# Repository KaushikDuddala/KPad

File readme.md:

# KPad v1!

The KPad is a simple macropad made by me just to learn the process and hopefully make revisions or a full keyboard in the future!! This was made using KMK, KiCad, Fusion 360, and more. 

## Features:

 - 128x32 OLED with volume display
 - EC11 Encoder for Volume
 - 16 SK6812 LEDs for underglow!!
 - 8 keys + physical key in the ec11
 - KMK firmware

 ## Future Features:
 - Swappable Modes (Single key swaps a mode that chaanges all key functions)
 - VIA support
 - Better software LED control
 - Better case design
 - Acrylic rather than hole in case

## Final Design

## PCB Design:

## Case:

## Bill of Materials (BOM):

- x9 1N4148 Diodes
- x8 Cherry MX switches
- x8 Keycaps
- x1 EC11 Encoder w/ switch
- x1 128x32 0.91" OLED screen
- x1 Seeed Studio XIAO RP2040
- x16 SK6812 LEDs
- x1 Case (2 3d printed halves)
- x4 M3x16mm Screws
- x4 M3x5mmx4mm heatset inserts

|Id |Designator                                            |Footprint                                     |Quantity|Designation         |
|---|------------------------------------------------------|----------------------------------------------|--------|--------------------|
|1  |D22,D17,D18,D24,D19,D20,D23,D25,D21                   |D_DO-35_SOD27_P7.62mm_Horizontal              |9       |1N4148              |
|2  |SW3,SW9,SW4,SW6,SW8,SW5,SW7,SW2                       |SW_Cherry_MX_1.00u_PCB                        |8       |SW_Push             |
|3  |SW1                                                   |RotaryEncoder_Alps_EC11E-Switch_Vertical_H20mm|1       |RotaryEncoder_Switch|
|4  |J1                                                    |SSD1306-0.91-OLED-4pin-128x32                 |1       |Conn_01x04          |
|5  |U1                                                    |XIAO-RP2040-DIP                               |1       |XIAO-RP2040-DIP     |
|6  |D9,D4,D15,D7,D12,D2,D14,D3,D13,D8,D6,D11,D10,D1,D5,D16|LED_SK6812MINI_PLCC4_3.5x3.5mm_P1.75mm        |16      |SK6812MINI          |

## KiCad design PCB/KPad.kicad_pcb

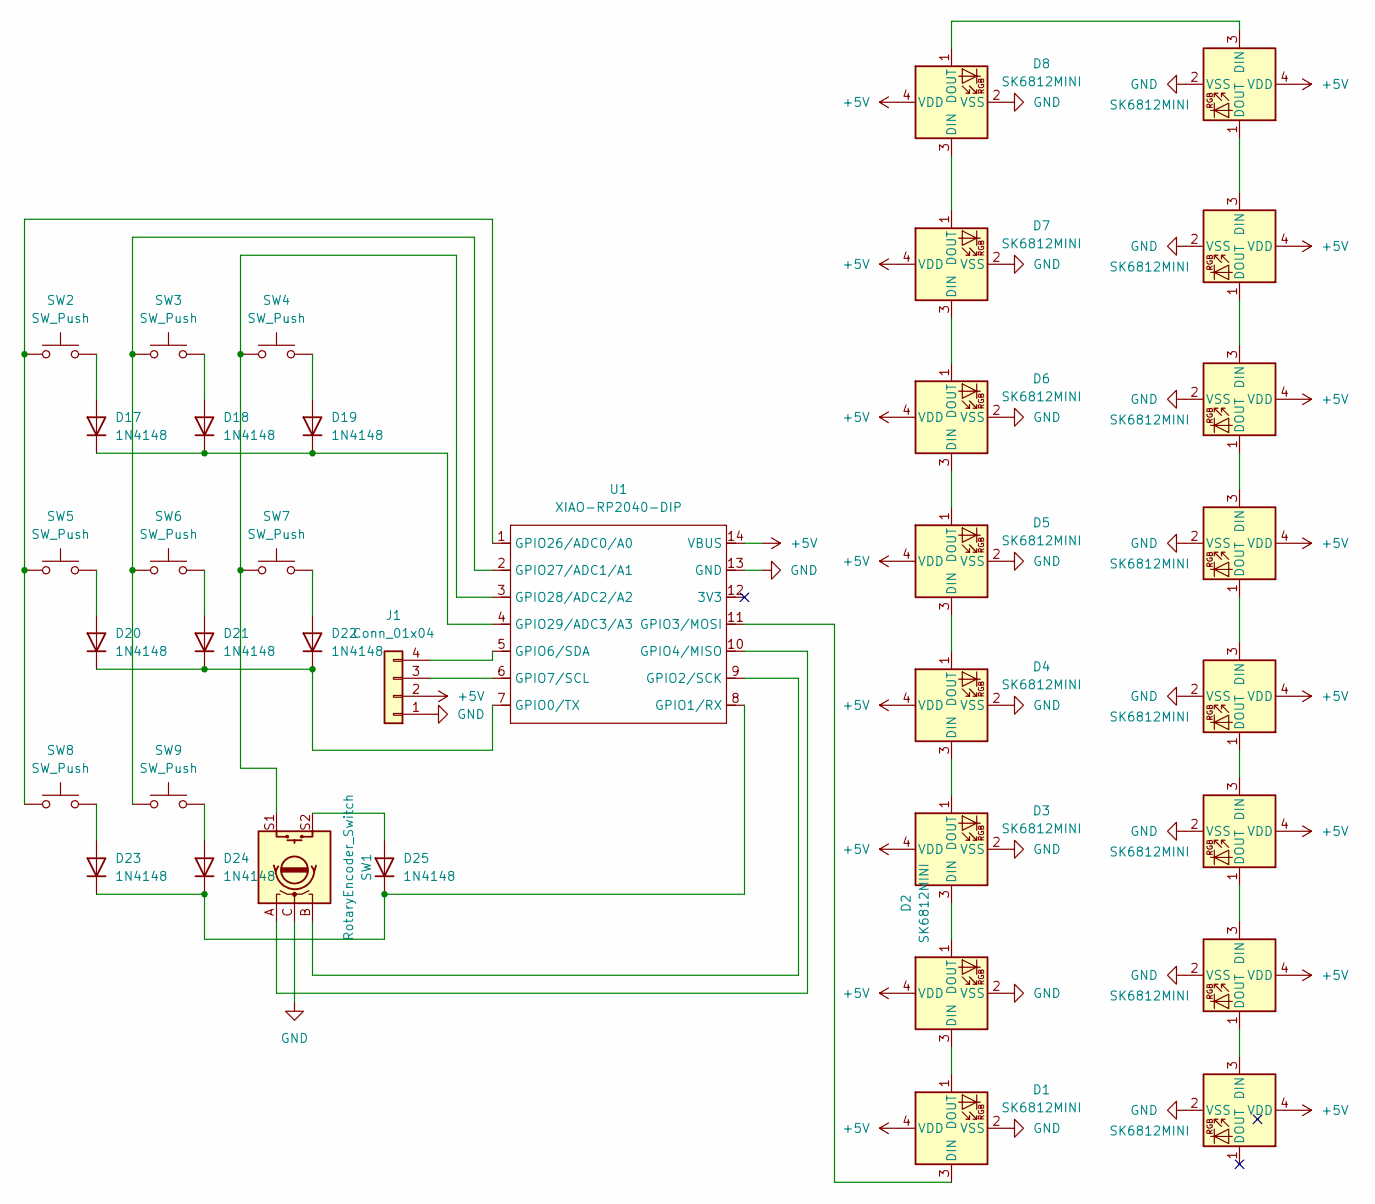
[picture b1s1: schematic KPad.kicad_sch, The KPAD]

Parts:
D1, D2, D3, D4, D5, D6, D7, D8, D9, D10, D11, D12, D13, D14, D15, D16: SK6812MINI; LED_SK6812MINI_PLCC4_3.5x3.5mm_P1.75mm
D17, D18, D19, D20, D21, D22, D23, D24, D25: 1N4148; D_DO-35_SOD27_P7.62mm_Horizontal
J1: Conn_01x04; SSD1306-0.91-OLED-4pin-128x32
SW1: RotaryEncoder_Switch; RotaryEncoder_Alps_EC11E-Switch_Vertical_H20mm
SW2, SW3, SW4, SW5, SW6, SW7, SW8, SW9: SW_Push; SW_Cherry_MX_1.00u_PCB
U1: XIAO-RP2040-DIP

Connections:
+5V: D1.4 (VDD), D2.4 (VDD), D3.4 (VDD), D4.4 (VDD), D5.4 (VDD), D6.4 (VDD), D7.4 (VDD), D8.4 (VDD), D9.4 (VDD), D10.4 (VDD), D11.4 (VDD), D12.4 (VDD), D13.4 (VDD), D14.4 (VDD), D15.4 (VDD), D16.4 (VDD), J1.2, U1.14 (VBUS)
GND: D1.2 (VSS), D2.2 (VSS), D3.2 (VSS), D4.2 (VSS), D5.2 (VSS), D6.2 (VSS), D7.2 (VSS), D8.2 (VSS), D9.2 (VSS), D10.2 (VSS), D11.2 (VSS), D12.2 (VSS), D13.2 (VSS), D14.2 (VSS), D15.2 (VSS), D16.2 (VSS), J1.1, SW1.C, U1.13 (GND)
unnamed: D1.3 (DIN), U1.11 (GPIO3/MOSI)
unnamed: D1.1 (DOUT), D2.3 (DIN)
unnamed: D2.1 (DOUT), D3.3 (DIN)
unnamed: D3.1 (DOUT), D4.3 (DIN)
unnamed: D4.1 (DOUT), D5.3 (DIN)
unnamed: D5.1 (DOUT), D6.3 (DIN)
unnamed: D6.1 (DOUT), D7.3 (DIN)
unnamed: D7.1 (DOUT), D8.3 (DIN)
unnamed: D8.1 (DOUT), D9.3 (DIN)
unnamed: D9.1 (DOUT), D10.3 (DIN)
unnamed: D10.1 (DOUT), D11.3 (DIN)
unnamed: D11.1 (DOUT), D12.3 (DIN)
unnamed: D12.1 (DOUT), D13.3 (DIN)
unnamed: D13.1 (DOUT), D14.3 (DIN)
unnamed: D14.1 (DOUT), D15.3 (DIN)
unnamed: D15.1 (DOUT), D16.3 (DIN)
unnamed: D17.2 (A), SW2.2
unnamed: D17.1 (K), D18.1 (K), D19.1 (K), U1.4 (GPIO29/ADC3/A3)
unnamed: D18.2 (A), SW3.2
unnamed: D19.2 (A), SW4.2
unnamed: D20.2 (A), SW5.2
unnamed: D20.1 (K), D21.1 (K), D22.1 (K), U1.7 (GPIO0/TX)
unnamed: D21.2 (A), SW6.2
unnamed: D22.2 (A), SW7.2
unnamed: D23.2 (A), SW8.2
unnamed: D23.1 (K), D24.1 (K), D25.1 (K), U1.8 (GPIO1/RX)
unnamed: D24.2 (A), SW9.2
unnamed: D25.2 (A), SW1.S2
unnamed: J1.3, U1.6 (GPIO7/SCL)
unnamed: J1.4, U1.5 (GPIO6/SDA)
unnamed: SW1.B, U1.9 (GPIO2/SCK)
unnamed: SW1.A, U1.10 (GPIO4/MISO)
unnamed: SW2.1, SW5.1, SW8.1, U1.1 (GPIO26/ADC0/A0)
unnamed: SW3.1, SW6.1, SW9.1, U1.2 (GPIO27/ADC1/A1)
unnamed: SW1.S1, SW4.1, SW7.1, U1.3 (GPIO28/ADC2/A2)

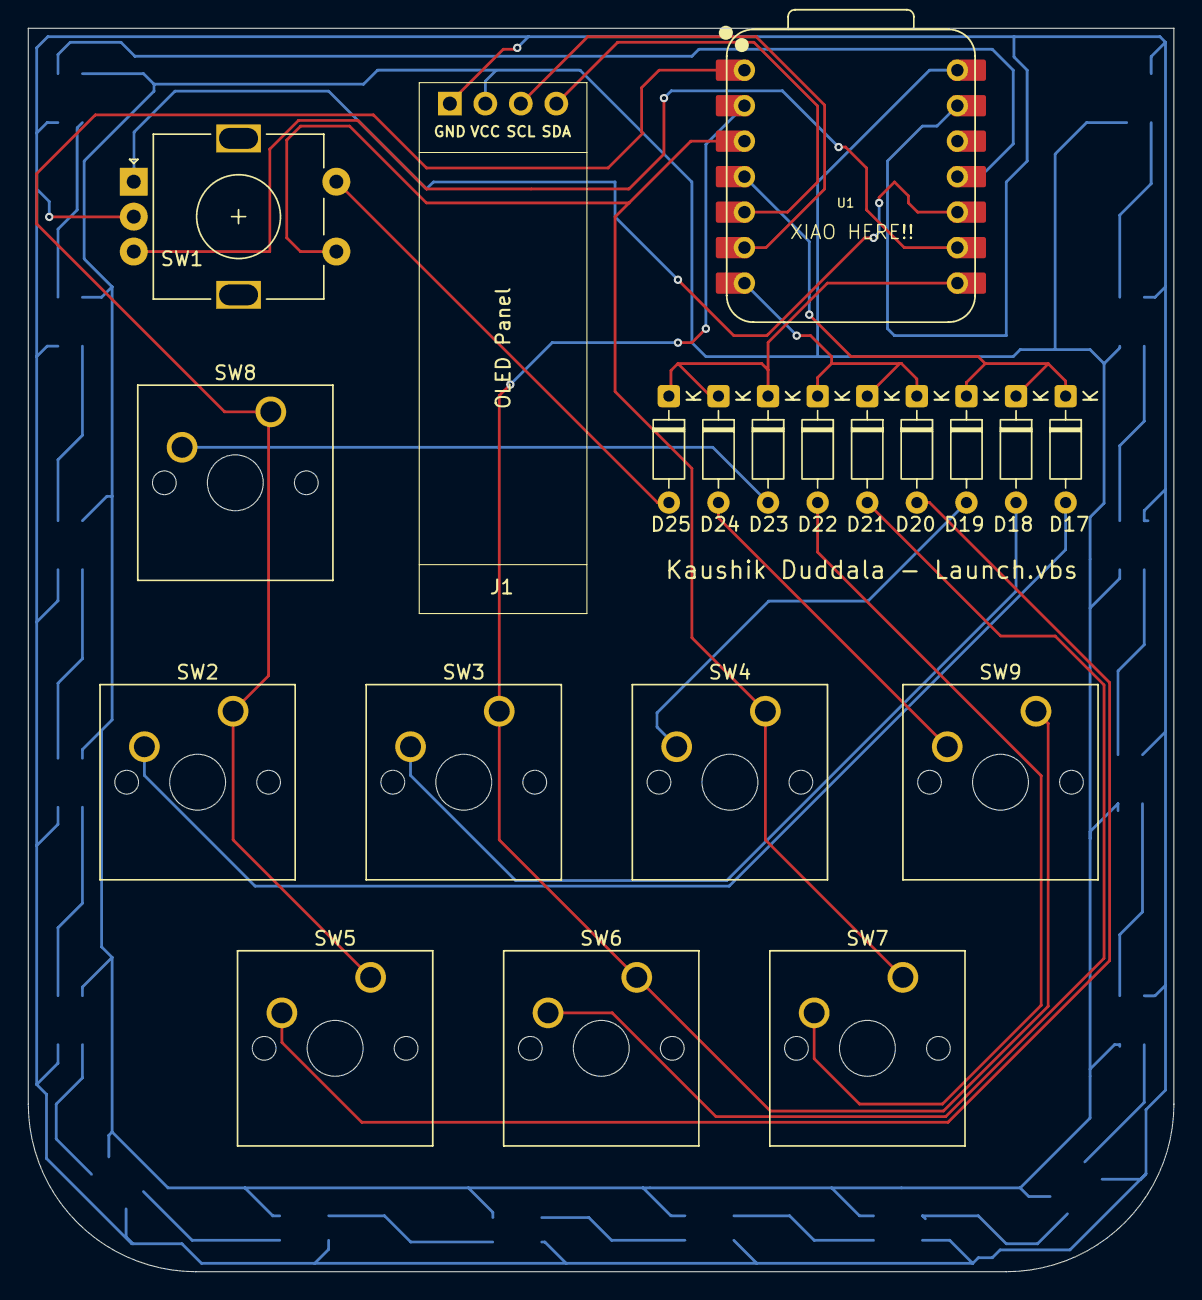
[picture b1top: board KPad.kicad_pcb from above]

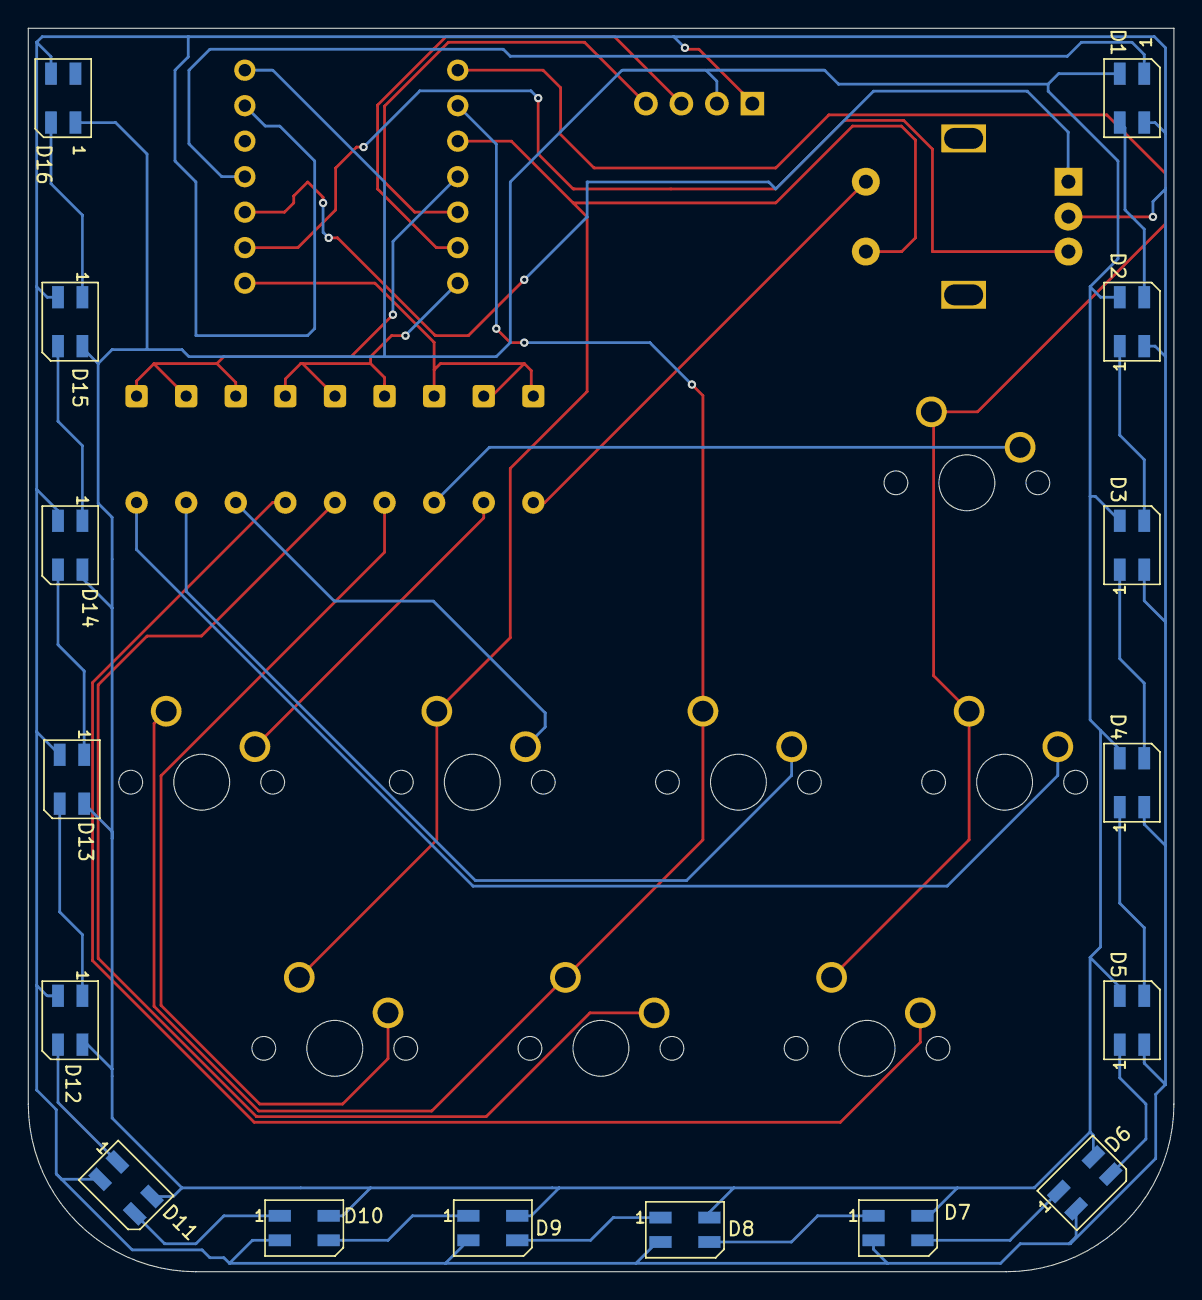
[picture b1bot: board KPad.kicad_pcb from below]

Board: 2 copper layers, 82.0 x 89.0 mm, 36 parts (16 on the bottom side), 37 nets.

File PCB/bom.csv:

Id,Designator,Footprint,Quantity,Designation
1,"D22,D17,D18,D24,D19,D20,D23,D25,D21",D_DO-35_SOD27_P7.62mm_Horizontal,9,1N4148
2,"SW3,SW9,SW4,SW6,SW8,SW5,SW7,SW2",SW_Cherry_MX_1.00u_PCB,8,SW_Push
3,SW1,RotaryEncoder_Alps_EC11E-Switch_Vertical_H20mm,1,RotaryEncoder_Switch
4,J1,SSD1306-0.91-OLED-4pin-128x32,1,Conn_01x04
5,U1,XIAO-RP2040-DIP,1,XIAO-RP2040-DIP
6,"D9,D4,D15,D7,D12,D2,D14,D3,D13,D8,D6,D11,D10,D1,D5,D16",LED_SK6812MINI_PLCC4_3.5x3.5mm_P1.75mm,16,SK6812MINI

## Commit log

2025-11-29 initial
2025-11-30 final??
2025-11-30 oops image links
2025-11-30 accidentally duplicated some stuff
2025-11-30 fix image link
2025-12-02 regen gerber with drill files?
